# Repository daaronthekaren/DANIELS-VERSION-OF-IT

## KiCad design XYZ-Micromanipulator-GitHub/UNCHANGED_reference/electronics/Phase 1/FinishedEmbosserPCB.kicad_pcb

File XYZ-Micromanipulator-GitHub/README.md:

# XYZ Micro-Manipulator: Slicer, 4th Focus Axis and FreeCAD Study

Senior design software work for the XYZ micro-manipulator: a corrected STL slicer, a separately controlled 4th (focus) axis in the GUI and G-code workflow, the FreeCAD CAM study (Item 8), and the firmware fixes those need.

## Folder layout

Top-level folder names show what happened to each part.

| Folder | Status | What it is |
|---|---|---|
| `EDITED_gui/` | edited | PySide6 control GUI with the focus axis, strict G-code runner and serial API (`source/`), plus 102 tests (`tests/`) |
| `EDITED_firmware/` | edited | RP2350 motion-controller firmware (PlatformIO project) |
| `NEW_slicer/` | new | `pbm_slicer.py` STL → G-code slicer, `verify_gcode.py`, 34 tests, `examples/` |
| `NEW_freecad_study/` | new | Item 8: FreeCAD project, its milling G-code, and the FreeCAD 1.0.2 rerun evidence |
| `NEW_docs/` | new | Write-ups, demonstration guide (`.md` and `.docx`), firmware build log, `images/` |
| `UNCHANGED_reference/` | unchanged | CAD (`construction`), `electronics`, `datasheets`, original `documentation`, `python_api`, `encoder_field_sim`, the embossing-machine project, team documents |

## New and edited code files

Code files keep their real names so imports and `#include`s work. This table is the label.

| Status | Files |
|---|---|
| **New** | `EDITED_gui/source/gcode_program.py`, `EDITED_gui/source/hardware/focus_axis.py`, `EDITED_gui/source/version.py`, `EDITED_gui/tests/*`, `EDITED_gui/requirements-dev.txt`, everything in `NEW_slicer/`, `NEW_freecad_study/`, `NEW_docs/` |
| **Edited** | `EDITED_gui/source/mainwindow.py`, `gcode_runner.py`, `main.py`, `hardware/open_micro_stage_api.py`, `gui_components/realtime_controller_widget.py`, `EDITED_gui/README.md` |
| **Edited (firmware)** | `EDITED_firmware/src/robot.cpp`, `robot.h`, `motion_control/motion_controller.cpp/.h`, `motion_control/path_segment.cpp`, `servo_control/homing_controller.cpp`, `command_parser/command_parser.cpp` |
| **Restored (firmware)** | `EDITED_firmware/src/version.h`, `src/utilities/{math3d.h, math_constants.h, ringbuffer.h, utilities.h, utilities.cpp, waveforms.h, waveforms.cpp}`, missing from the original copy, taken from upstream MicroManipulatorStepper commit `9d18a57` |

Every change, its reason and how it was verified: [`NEW_docs/correction_report.md`](NEW_docs/correction_report.md).
Where each file from the original GitHub project is now: [`README_CHANGES.txt`](README_CHANGES.txt).

## Quick start (Windows)

```
cd EDITED_gui
setup.bat
.venv\Scripts\python.exe -m pip install -r requirements-dev.txt
.venv\Scripts\python.exe source\main.py --simulate-focus
.venv\Scripts\python.exe -m pytest tests ..\NEW_slicer\tests -q
```

Slicer: `cd NEW_slicer` then `python pbm_slicer.py examples\block_with_hole.stl --preview`.
Firmware: open `EDITED_firmware` in VS Code with PlatformIO and build (needs Git with long paths enabled).

## Verification status

| Check | Result |
|---|---|
| Automated tests (pytest + pytest-qt) | 136 passed |
| Firmware build (`pio run -e pico`) | SUCCESS, RAM 4.9 %, flash 3.3 % (not flashed) |
| FreeCAD 1.0.2 rerun of the Item 8 job | Output identical to the stored G-code |
| GUI launch with `--simulate-focus` | Starts and runs |
| Hardware (stage, laser, Pi, focus motor) | **Not tested yet**; see `NEW_docs/fourth_axis_gui_writeup.md` |

## Documents

| Document | Content |
|---|---|
| [`NEW_docs/demonstration_guide.docx`](NEW_docs/demonstration_guide.docx) / [`.md`](NEW_docs/demonstration_guide.md) | Folder-by-folder guide: how, why, how to test, expected results, software |
| [`NEW_docs/item8_freecad_summary.md`](NEW_docs/item8_freecad_summary.md) | Item 8 FreeCAD CAM study summary |
| [`NEW_docs/slicer_writeup.md`](NEW_docs/slicer_writeup.md) | Slicer write-up |
| [`NEW_docs/fourth_axis_gui_writeup.md`](NEW_docs/fourth_axis_gui_writeup.md) | 4th-axis GUI write-up and physical checklist |
| [`NEW_docs/setup_and_verification.md`](NEW_docs/setup_and_verification.md) | Setup and reproduction commands |
| [`NEW_docs/correction_report.md`](NEW_docs/correction_report.md) | Problem → evidence → fix → verification |

## License

The GUI and firmware are based on the MIT-licensed Open Micro-Manipulator project; the original license headers are kept in those files (see `EDITED_gui/LICENSE`).

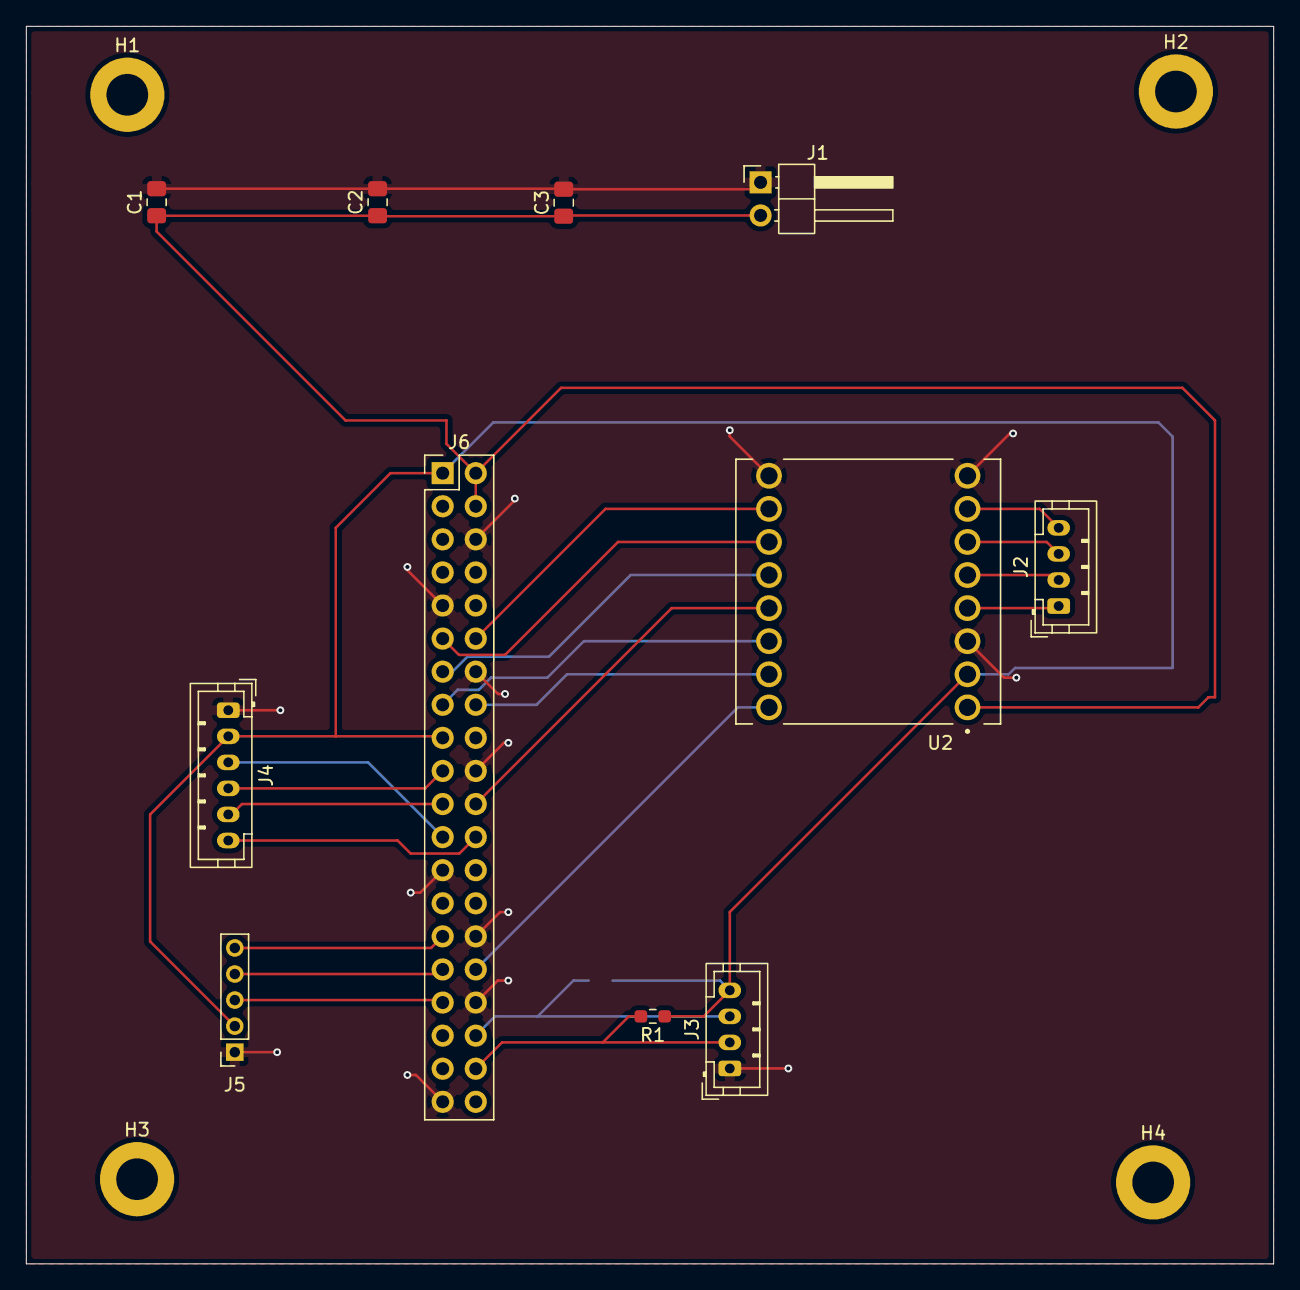
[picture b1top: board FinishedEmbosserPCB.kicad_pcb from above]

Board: 2 copper layers, 95.8 x 95.0 mm, 16 parts (1 on the bottom side), 23 nets.

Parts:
C1, C2, C3: 10uF 6V; C_0805_2012Metric_Pad1.18x1.45mm_HandSolder
H1, H2, H3, H4: MountingHole_Pad; MountingHole_3.2mm_M3_ISO7380_Pad
J1: Power 5V; PinHeader_1x02_P2.54mm_Horizontal
J2, J3: Motor; JST_PH_B4B-PH-K_1x04_P2.00mm_Vertical
J4: Conn_01x06_Pin; JST_PH_B6B-PH-K_1x06_P2.00mm_Vertical
J5: Conn_01x05_Pin; PinSocket_1x05_P2.00mm_Vertical
J6: Raspberry_Pi_2_3; PinHeader_2x20_P2.54mm_Vertical
R1, R2: 4K7; R_0603_1608Metric_Pad0.98x0.95mm_HandSolder
U2: ROB-14450; MODULE_ROB-14450

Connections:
+3.3V: J3.4, J4.2, J5.2, J6.1 (3V3), J6.17 (3V3), R1.1, R2.1, U2.2 (VCC)
+5V: C1.1, C2.1, C3.1, J1.2, J6.2 (5V), J6.4 (5V), U2.1 (VM)
/CLK: J4.3, J6.23 (SCLK0/GPIO11)
/CS: J4.6, J6.24 (~CE0/GPIO8)
/GPIO0: J5.5, J6.29 (GCLK1/GPIO5)
/GPIO1: J5.4, J6.31 (GCLK2/GPIO6)
/GPIO2: J5.3, J6.33 (PWM1/GPIO13)
/IO1: J3.2, J6.38 (GPIO20/MOSI1), R1.2
/IO2: J3.3, J6.36 (GPIO16), R2.2
/MA1: J2.1, U2.4 (A01)
/MA2: J2.2, U2.5 (A02)
/MB1: J2.4, U2.7 (B01)
/MB2: J2.3, U2.6 (B02)
/MISO: J4.5, J6.21 (MISO0/GPIO9)
/MOSI: J4.4, J6.19 (MOSI0/GPIO10)
/Motor_EN: J6.22 (GPIO25), U2.13 (STBY)
/Motor_MA1: J6.15 (GPIO22), U2.14 (AI1)
/Motor_MA2: J6.16 (GPIO23), U2.15 (AI2)
/Motor_MB1: J6.13 (GPIO27), U2.12 (BI1)
/Motor_MB2: J6.11 (GPIO17), U2.11 (BI2)
/Motor_PWMA: J6.32 (PWM0/GPIO12), U2.16 (PWMA)
/Motor_PWMB: J6.12 (GPIO18/PWM0), U2.10 (PWMB)
GND: C1.2, C2.2, C3.2, J1.1, J3.1, J4.1, J5.1, J6.6 (GND), J6.9 (GND), J6.14 (GND), J6.20 (GND), J6.25 (GND), J6.30 (GND), J6.34 (GND), J6.39 (GND), U2.3 (GND), U2.8 (GND), U2.9 (GND)
